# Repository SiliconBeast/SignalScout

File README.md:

# Signal Scout

A pocket RF field instrument: Wi-Fi/Bluetooth diagnostics, broadband RF presence sensing and a GPS + LoRa mesh safety beacon in one handheld. Hardware, enclosure and firmware live in this repository.

It runs **SignalOS**: a lock screen and always-on display, a pull-down shade, notifications, gestures with button equivalents, and two profiles (Hackerspace and Adventure). It joins Wi-Fi for time, weather and over-the-air updates. Design notes: [docs/SIGNALOS.md](docs/SIGNALOS.md).

| Hackerspace | Today | Shade | Always-on | Adventure | Weather |
|---|---|---|---|---|---|
|  |  |  |  |  |  |

**Try it in a browser:** `web/` is the real SignalOS UI compiled to WebAssembly inside a clickable device frame, with touch and gestures. Run `python3 -m http.server -d web 8000` and open http://localhost:8000. Rebuild it with `tools/build_web.sh` (needs `pip install ziglang`).

All 30 screens are in [docs/screenshots](docs/screenshots). The simulator renders them from the same UI code that runs on the device, driving it with scripted button presses and touch gestures.

## Hardware

**Base unit** (`SignalScout_Base/`, 46 x 82 mm, 4-layer)

| Function | Part |
|---|---|
| MCU | ESP32-S3-WROOM-1-N16R8 |
| Display | TOQ206XVT-01 2.06" AMOLED, QSPI |
| LoRa | Ebyte E22-900M22S (SX1262), 915 MHz |
| GNSS | u-blox MAX-M10S |
| Inputs | D-pad, A, B, side, SOS, lock slide switch (AW9523B expander) |
| Sensors | LSM6DSO IMU, BME280 |
| Feedback | DRV2605L + LRA, PAM8904 + piezo siren, RGB LED |
| Power | BQ24074 charger, MAX17048 fuel gauge, TPS63001 3.3 V |
| I/O | microSD, Qwiic, USB-C, pogo link to the sled |

**Sled** (`SignalScout_Sled.kicad_pcb`): carries the Arduino UNO Q and an AD8317 log detector (1 MHz to 10 GHz) on a U.FL antenna, plus its own battery, charger and 5 V boost. It links to the base through pogo pins: UART, I2C (sled ID EEPROM and fuel gauge) and a wake line.

**Enclosure**: `enclosure/` (STEP and STL).

### Pin map

Generated from the KiCad boards by `tools/gen_pins.py`, which also writes `firmware/include/pins.h`. The board files are the source of truth.

<!-- PINMAP:BEGIN -->
#### ESP32-S3-WROOM-1 (base board U1)

| Net | Module pad | GPIO | Note |
|---|---|---|---|
| `SD_CS` | 27 | IO0 | Strapping pin: boot mode |
| `LORA_RXEN` | 39 | IO1 |  |
| `GNSS_TXD` | 38 | IO2 |  |
| `SIREN_PWM` | 15 | IO3 | Strapping pin: JTAG select |
| `I2C_SDA` | 4 | IO4 |  |
| `I2C_SCL` | 5 | IO5 |  |
| `TP_INT` | 6 | IO6 |  |
| `DISP_TE` | 7 | IO7 |  |
| `DISP_RESET` | 12 | IO8 |  |
| `LCD_D3` | 17 | IO9 |  |
| `LCD_CS` | 18 | IO10 |  |
| `LCD_D0` | 19 | IO11 |  |
| `LCD_SCK` | 20 | IO12 |  |
| `LCD_D1` | 21 | IO13 |  |
| `LCD_D2` | 22 | IO14 |  |
| `EXP_INT` | 8 | IO15 |  |
| `SPI_MISO` | 9 | IO16 |  |
| `SPI_MOSI` | 10 | IO17 |  |
| `SPI_SCK` | 11 | IO18 |  |
| `USB_D-` | 13 | IO19 |  |
| `USB_D+` | 14 | IO20 |  |
| `KEY_SOS` | 23 | IO21 |  |
| `LORA_NSS` | 31 | IO38 |  |
| `LORA_BUSY` | 32 | IO39 |  |
| `LORA_DIO1` | 33 | IO40 |  |
| `LORA_NRST` | 34 | IO41 |  |
| `GNSS_RXD` | 35 | IO42 |  |
| `SLED_TX` | 37 | IO43 |  |
| `SLED_RX` | 36 | IO44 |  |
| `HAPTIC_EN` | 26 | IO45 | Strapping pin: VDD_SPI voltage |
| `SIREN_EN` | 16 | IO46 | Strapping pin: boot mode / ROM log |
| `SLED_SDA` | 24 | IO47 |  |
| `SLED_SCL` | 25 | IO48 |  |

#### AW9523B I/O expander (base board U4, I2C 0x58)

| Net | Port pin |
|---|---|
| `KEY_UP` | P0_0 |
| `KEY_DOWN` | P0_1 |
| `KEY_LEFT` | P0_2 |
| `KEY_RIGHT` | P0_3 |
| `KEY_A` | P0_4 |
| `KEY_B` | P0_5 |
| `SPARE_IO` | P0_6 |
| `KEY_SIDE` | P0_7 |
| `KEY_LOCK` | P1_0 |
| `CHG_N` | P1_1 |
| `SLED_WAKE` | P1_2 |
| `DISP_PWR_EN` | P1_3 |
| `GNSS_RST` | P1_4 |
| `LED_RK` | P1_5 |
| `LED_GK` | P1_6 |
| `LED_BK` | P1_7 |

#### UNO Q headers (sled A1)

| Net | UNO pin |
|---|---|
| `AD_VOUT` | A0 |
| `UNOQ_RX` | D0 |
| `UNOQ_TX` | D1 |
| `UNOQ_WAKE` | D2 |
<!-- PINMAP:END -->

## What it does

**Wi-Fi, Channels and Bluetooth** scan Wi-Fi and Bluetooth LE passively. Networks are listed by signal strength with channel, band and security. The Channels tab shows 2.4 GHz channel load and the least congested of channels 1/6/11. Press A on a network for its details and a signal-over-time graph.

**Sweep** shows the broadband RF level from the sled's detector as a number, a meter and a 30-second history. The level is compared with the Wi-Fi/BLE emitters the unit can see:

- *Quiet*: at the noise floor.
- *Explained*: consistent with the visible Wi-Fi/BLE activity.
- *Unexplained*: clearly more energy than the visible emitters account for.

It reports how much energy is present, not what the source is. The detector is broadband, so it cannot tell frequency or identify a transmitter.

**Position, Navigate and Mesh** show the GNSS fix, save waypoints, and point back to a saved waypoint with distance and bearing. It sends short text messages over a LoRa mesh (no subscription, peer to peer). Holding the SOS button for 2 seconds broadcasts the position to the mesh every 20 seconds and sounds the siren; hold again to cancel. SOS works from any screen and with the lock switch on.

**Weather** shows the online forecast (hourly and 3 days, Open-Meteo) when the unit is on Wi-Fi. It always shows a barometer forecast from the BME280 pressure trend, which works offline.

**Console** starts a hotspot with a join QR code. From any browser you can download logs and waypoints, add Wi-Fi networks, edit settings and upload firmware.

**Updates** checks GitHub releases. The download goes to the spare flash slot and is verified with SHA-256, and the bootloader rolls back automatically if the new version fails.

**Also**: Torch (white or red), Level, Settings, status bar with a live-activity pill, deep sleep, CSV logs on the card.

**Scope**: receive and analyse, plus the unit's own LoRa messages. The firmware has no deauthentication, jamming or spoofing features.

### Controls

| Control | Action |
|---|---|
| D-pad | Move focus; Left/Right switch tabs or change a setting |
| A | Select; hold on an app icon for quick actions; unlock |
| B | Back; hold for home |
| Side button | Home; on the launcher, opens the shade |
| SOS (hold 2 s) | Start or cancel SOS |
| Lock switch | Always-on display, keys ignored (SOS still works) |
| Touch | Tap; swipe down from the top for the shade, up from the bottom for home, right from the left edge for back; long-press an icon |

## What's next

Most new features can ship as over-the-air updates. First in line:

- **Safety:** Meshtastic compatibility, fall or crash detection with auto-SOS, a dead-man check-in timer, unknown BLE tracker detection.
- **Installers:** a Wi-Fi site-survey heat map, RF fingerprinting from detector burst timing, network health checks.
- **Outdoors:** breadcrumb track-back, GPX trips, offline maps, haptic navigation.
- **Platform:** a phone companion over BLE for free-text messages, and installable script apps.

Hardware additions (magnetometer, SDR, NFC, satellite) would come as sleds. Full list: [docs/ROADMAP.md](docs/ROADMAP.md).

## Repository layout

| Path | Contents |
|---|---|
| `firmware/` | ESP32-S3 firmware, simulator and unit tests (PlatformIO) |
| `firmware/lib/ss_core` | Portable logic: pogo protocol, mesh, correlation, battery, geo, UBX, weather, OTA manifest, JSON, calendar |
| `firmware/lib/ss_services` | Services, one per subsystem, running on the HAL |
| `firmware/lib/ss_ui` | SignalOS (LVGL 9): shell, apps, theme, generated fonts and icons |
| `firmware/lib/ss_mock` | Mock for every HAL interface (simulator and tests) |
| `firmware/src/device` | ESP32-S3 drivers and FreeRTOS tasks |
| `firmware/src/sim` | Desktop simulator and screenshot renderer |
| `firmware/src/web`, `web/` | Browser simulator (WebAssembly) in a device frame |
| `sled/signalscout_sled` | Arduino App Lab app for the UNO Q (sketch + Python) |
| `assets/` | Icon tiles (PNG, both profiles) and fonts (OFL) |
| `docs/` | [SignalOS](docs/SIGNALOS.md), [roadmap](docs/ROADMAP.md), [bring-up checklist](docs/BRINGUP.md), [protocol](docs/PROTOCOL.md), [hardware-verification list](docs/TODO.md), [pin map](docs/PINMAP.md) |
| `tools/` | Pin-map, icon, font and test-vector generators, shared-file sync, release manifest |

## Firmware design

- **PlatformIO + Arduino-ESP32.** The Arduino core gives working Wi-Fi scan, NimBLE, SD and RadioLib support with little glue. The one place where it would cost performance, the QSPI display, uses the ESP-IDF SPI driver directly (`src/device/display.cpp`), which the Arduino core exposes.
- **HAL.** `lib/ss_core/hal.h` has one interface per peripheral. Device implementations are in `src/device`, mocks in `lib/ss_mock`.
- **Services.** One per subsystem (input, housekeeping, scan, sweep, GNSS, mesh, storage, network). On the device each runs in its own FreeRTOS task.
- **Display.** Two 40-row DMA buffers so LVGL renders while the previous strip is on the wire; brightness changes are applied between flushes.
- **Message bus.** The UI pops `Event`s and pushes `Cmd`s and never touches a driver or a service.
- **LoRa mesh.** RadioLib SX1262 at 500 kHz bandwidth, SF9. Managed flooding with a hop limit, duplicate suppression, random relay delay, SOS priority and a self-imposed 10 % airtime budget (SOS may exceed it).
- **GNSS.** UBX only: CFG-VALSET at boot (NAV-PVT at 1 Hz, GPS + Galileo + BeiDou, optional power save).
- **Sled.** The STM32 samples the detector and streams it to the base. The Linux side scans Wi-Fi/BLE and sends a verdict. If the Linux side is not running, the base runs the same comparison on its own scan.

## Build and flash

Install [PlatformIO Core](https://docs.platformio.org/en/latest/core/installation/index.html), then from `firmware/`:

```sh
pio run -e device                 # build
pio run -e device -t upload       # flash over USB-C
pio device monitor                # serial log (USB CDC)
pio test -e native                # unit tests on the host
pio run -e sim                    # simulator (needs libsdl2-dev)
.pio/build/sim/program            # interactive: arrows, Z = A, X = B, H = side, S = SOS, L = lock, mouse = touch
.pio/build/sim/program --shots ../docs/screenshots
```

If the board does not enter the bootloader by itself, hold BOOT, tap EN, release BOOT.

A plain CMake build of the tests and simulator is also available (`firmware/CMakeLists.txt`).

**Sled**: open `sled/signalscout_sled` in Arduino App Lab and run it on the UNO Q. Run `python3 tools/sync_shared.py` first if you changed `proto.h`.

After a hardware change run `python3 tools/gen_pins.py`. Do not edit `pins.h` by hand. Icons: `python3 tools/gen_icons.py`; fonts: `tools/gen_fonts.sh` (needs `npm i -g lv_font_conv`).

**Releases**: bump `SS_FW_VERSION` in `firmware/include/board.h`, then tag `v<version>`. The release workflow publishes `firmware.bin` and `manifest.json`, and devices offer the update.

## Status and known limitations

The logic, UI and protocol are tested on the host (39 firmware tests, 7 sled tests) and the device firmware builds in CI. **Nothing here has run on the real boards yet.** Follow [docs/BRINGUP.md](docs/BRINGUP.md) for first power-on; [docs/TODO.md](docs/TODO.md) lists what needs hardware to confirm.

- The display driver assumes the panel uses a CO5300 controller at 410 x 502 with a 22-column offset. Confirm against the panel datasheet.
- The Sweep detector is broadband and uncalibrated until the constants in the sled sketch are set against a known source.
- The navigation arrow uses GPS course over ground, so it only settles while moving. There is no magnetometer.
- Messages are canned quick replies; there is no keyboard.
- Touch assumes an FT3168 or CST816 class controller (both probed) with axes matching the panel. Confirm during bring-up.
- Over-the-air updates need a published release; until then the Updates app reports that it couldn't check.
- LoRa settings target the 902 to 928 MHz band (Canada/US). Check local rules before using it elsewhere.

## Contributing

See [CONTRIBUTING.md](CONTRIBUTING.md). Report security problems as described in [SECURITY.md](SECURITY.md).

## License

MIT, Copyright (c) 2026 Suvir Duggal. See [LICENSE](LICENSE). Covers the firmware, tools, PCB and enclosure files, and docs. The bundled Space Grotesk and JetBrains Mono fonts keep their own SIL Open Font License (see `assets/fonts/`).

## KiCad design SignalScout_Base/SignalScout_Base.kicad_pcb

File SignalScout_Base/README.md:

# Base board

KiCad project for the base unit (46 x 82 mm, 4-layer): ESP32-S3, AMOLED display, LoRa, GNSS, sensors, inputs and power.

Schematic sheets: `mcu`, `display`, `radio`, `sensors`, `controls`, `power`. Pin assignments are exported to the firmware by `tools/gen_pins.py`.

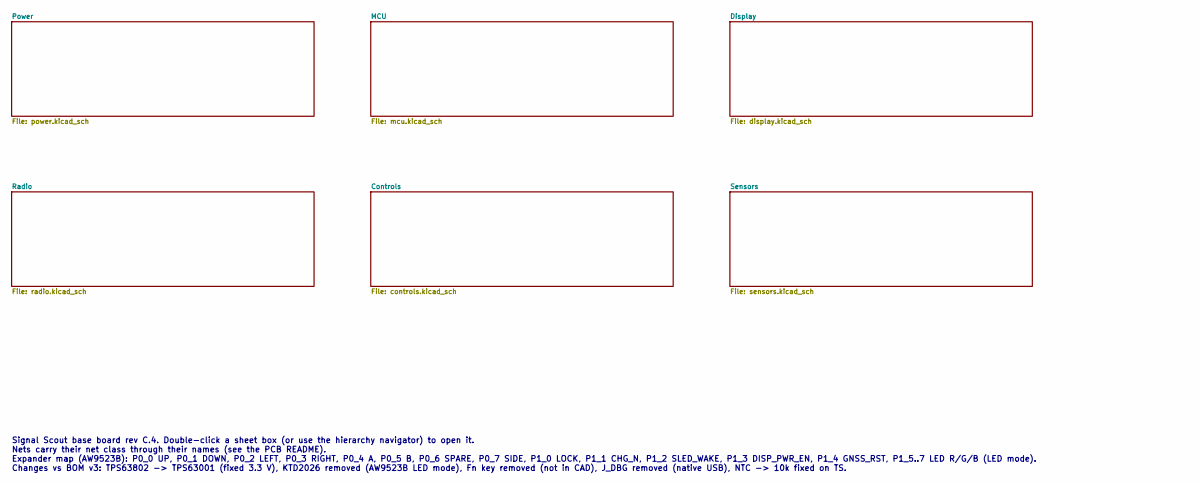
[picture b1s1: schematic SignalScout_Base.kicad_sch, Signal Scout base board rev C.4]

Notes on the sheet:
Signal Scout base board rev C.4. Double-click a sheet box (or use the hierarchy navigator) to open it. Nets carry their net class through their names (see the PCB README). Expander map (AW9523B): P0_0 UP, P0_1 DOWN, P0_2 LEFT, P0_3 RIGHT, P0_4 A, P0_5 B, P0_6 SPARE, P0_7 SIDE, P1_0 LOCK, P1_1 CHG_N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

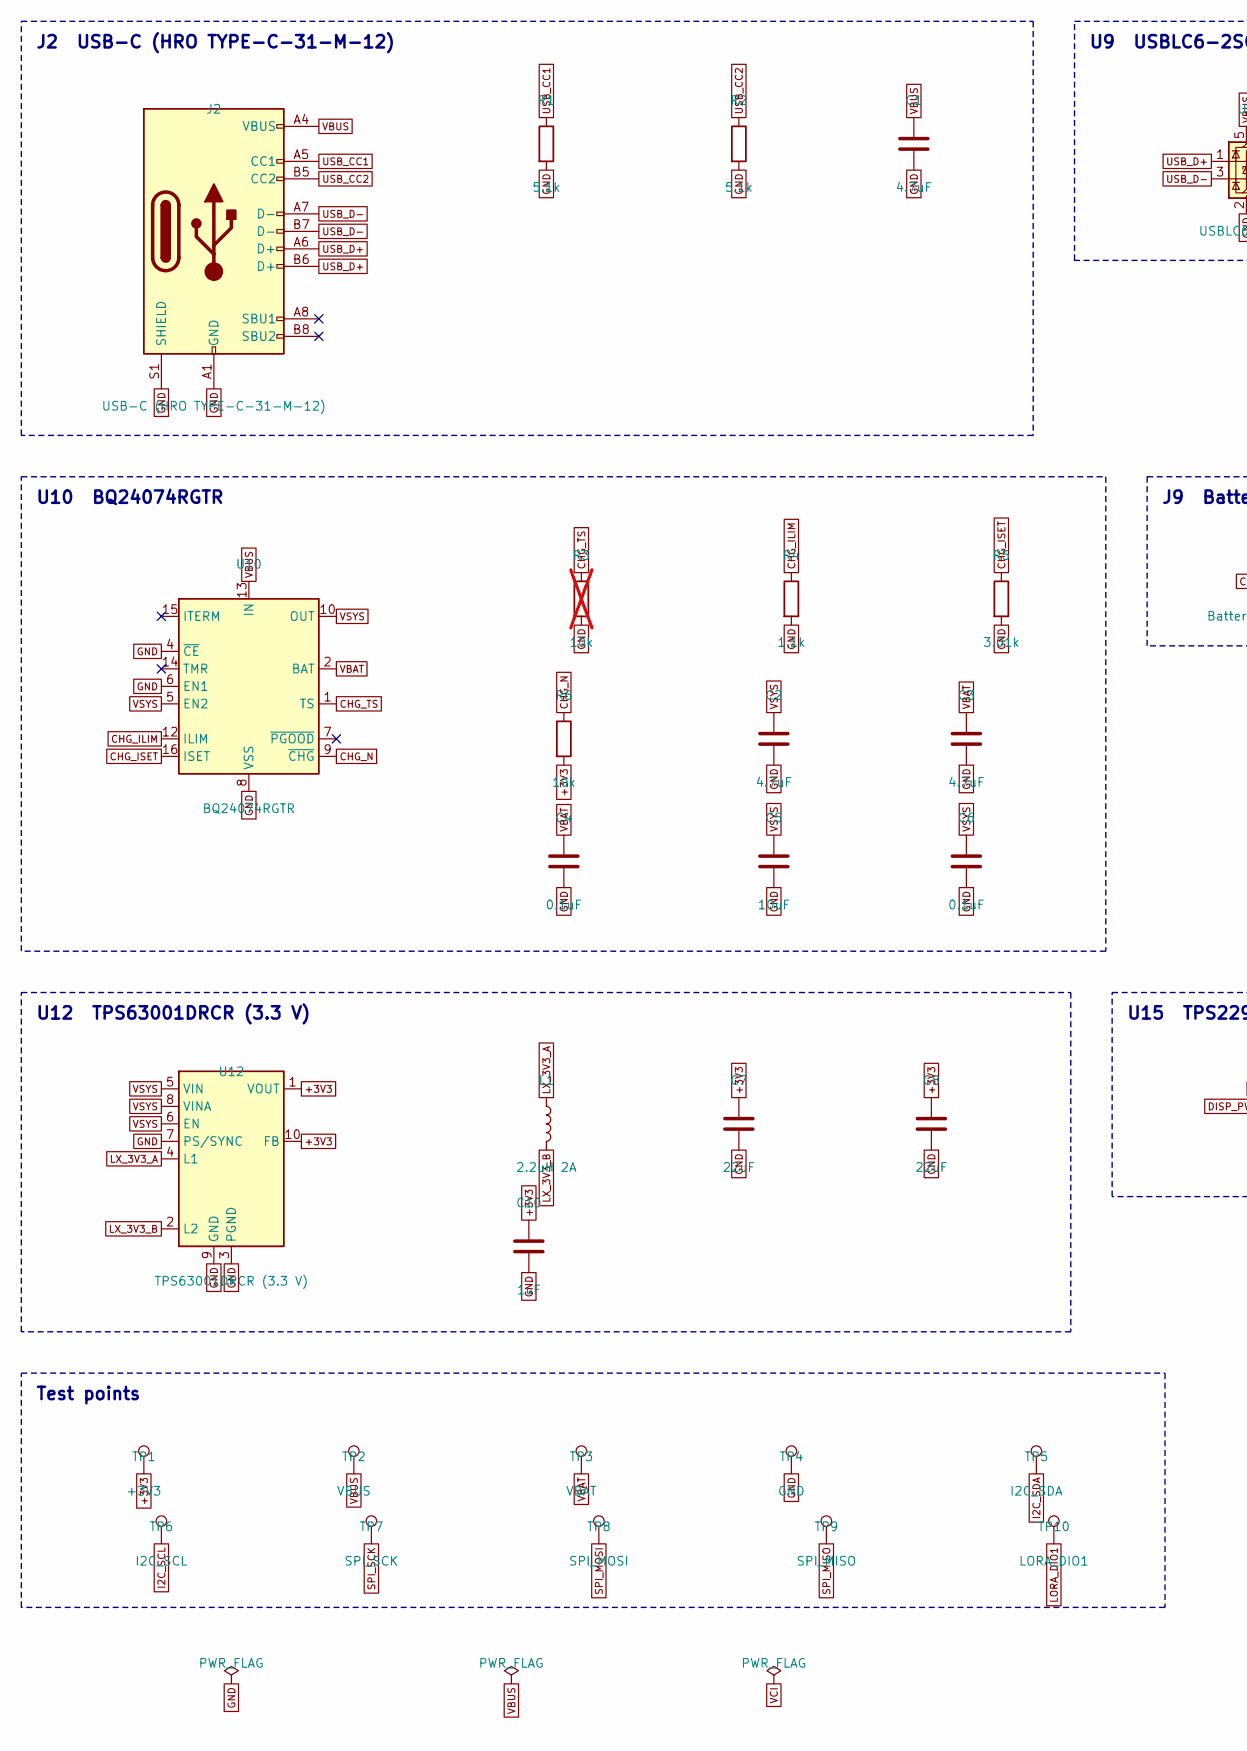
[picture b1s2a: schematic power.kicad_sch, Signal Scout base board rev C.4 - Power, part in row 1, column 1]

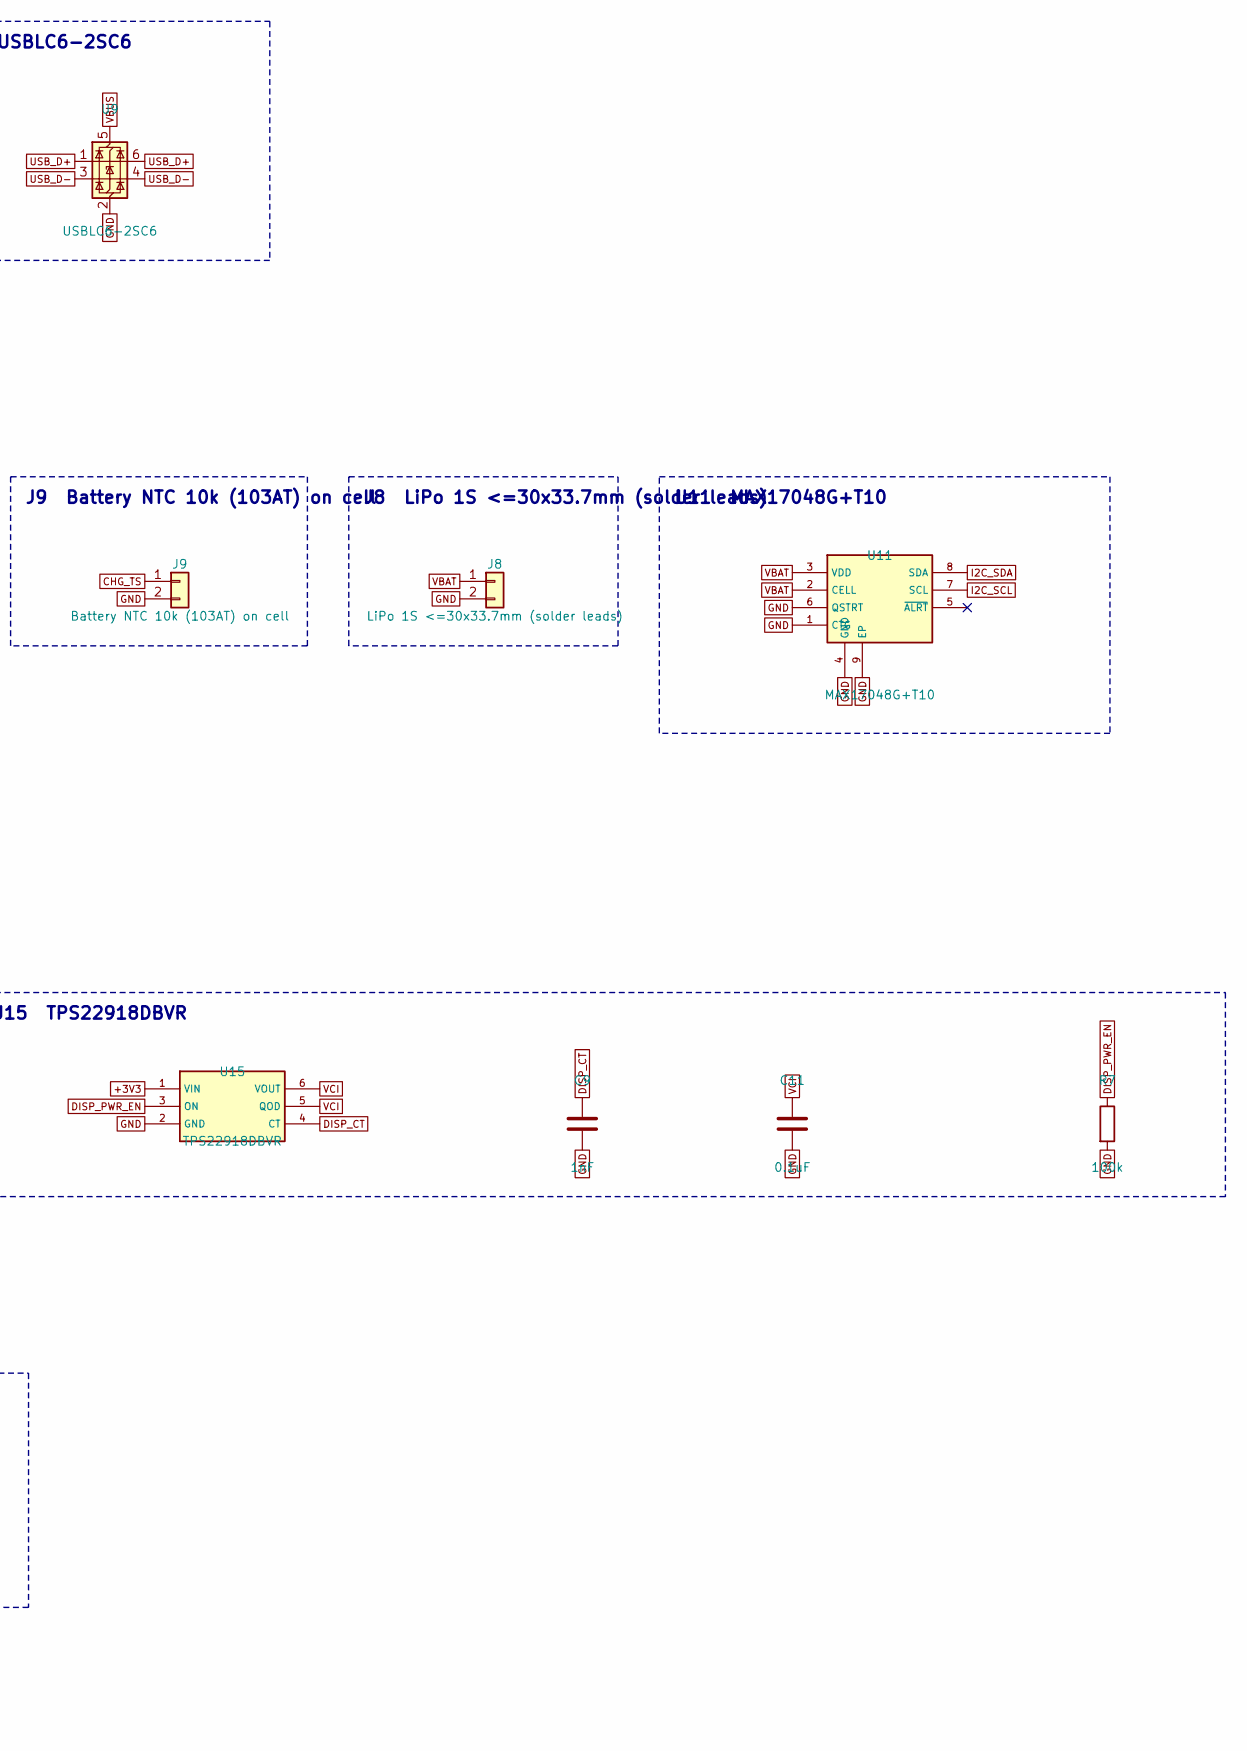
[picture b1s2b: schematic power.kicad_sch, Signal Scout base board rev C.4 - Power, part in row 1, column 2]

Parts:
C1, C2, C3: 4.7uF; C_0603_1608Metric
C4, C6, C11: 0.1uF; C_0402_1005Metric
C5: 10uF; C_0805_2012Metric
C7, C8: 22uF; C_0805_2012Metric
C9: 1nF; C_0402_1005Metric
C10: 1uF; C_0402_1005Metric
J2: USB-C (HRO TYPE-C-31-M-12); USB_C_Receptacle_HRO_TYPE-C-31-M-12
J8: LiPo 1S <=30x33.7mm (solder leads); SolderWire-0.25sqmm_1x02_P4.2mm_D0.65mm_OD1.7mm
J9: Battery NTC 10k (103AT) on cell; JST_SH_SM02B-SRSS-TB_1x02-1MP_P1.00mm_Horizontal
L1: 2.2uH 2A; L_1210_3225Metric
R1, R2: 5.1k; R_0402_1005Metric
R3: 10k; R_0402_1005Metric; not fitted
R4: 1.1k; R_0402_1005Metric
R5: 3.01k; R_0402_1005Metric
R6: 10k; R_0402_1005Metric
R7: 100k; R_0402_1005Metric
TP1: +3V3; TestPoint_Pad_D1.0mm
TP2: VBUS; TestPoint_Pad_D1.0mm
TP3: VBAT; TestPoint_Pad_D1.0mm
TP4: GND; TestPoint_Pad_D1.0mm
TP5: I2C_SDA; TestPoint_Pad_D1.0mm
TP6: I2C_SCL; TestPoint_Pad_D1.0mm
TP7: SPI_SCK; TestPoint_Pad_D1.0mm
TP8: SPI_MOSI; TestPoint_Pad_D1.0mm
TP9: SPI_MISO; TestPoint_Pad_D1.0mm
TP10: LORA_DIO1; TestPoint_Pad_D1.0mm
U9: USBLC6-2SC6; SOT-23-6
U10: BQ24074RGTR; VQFN-16-1EP_3x3mm_P0.5mm_EP1.6x1.6mm
U11: MAX17048G+T10; TDFN-8-1EP_2x2mm_P0.5mm_EP0.8x1.2mm
U12: TPS63001DRCR (3.3 V); Texas_DRC0010J
U15: TPS22918DBVR; SOT-23-6

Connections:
+3V3: C7.1, C8.1, C10.1, R6.2, TP1.1, U12.1 (VOUT), U12.10 (FB), U15.1 (VIN); also elsewhere on the board
CHG_ILIM: R4.1, U10.12 (ILIM)
CHG_ISET: R5.1, U10.16 (ISET)
CHG_N: R6.1, U10.9 (~CHG); also elsewhere on the board
CHG_TS: J9.1, R3.1, U10.1 (TS)
DISP_CT: C9.1, U15.4 (CT)
DISP_PWR_EN: R7.1, U15.3 (ON); also elsewhere on the board
GND: C1.2, C2.2, C3.2, C4.2, C5.2, C6.2, C7.2, C8.2, C9.2, C10.2, C11.2, J2.A1 (GND), J2.A12 (GND), J2.B1 (GND), J2.B12 (GND), J2.S1 (SHIELD), J8.2, J9.2, R1.2, R2.2, R3.2, R4.2, R5.2, R7.2, TP4.1, U9.2 (GND), U10.4 (~CE), U10.6 (EN1), U10.8 (VSS), U10.17 (VSS), U11.1 (CTG), U11.4 (GND), U11.6 (QSTRT), U11.9 (EP), U12.3 (PGND), U12.7 (PS/SYNC), U12.9 (GND), U12.11 (PGND), U15.2 (GND); also elsewhere on the board
I2C_SCL: TP6.1, U11.7 (SCL); also elsewhere on the board
I2C_SDA: TP5.1, U11.8 (SDA); also elsewhere on the board
LORA_DIO1: TP10.1; also elsewhere on the board
LX_3V3_A: L1.1, U12.4 (L1)
LX_3V3_B: L1.2, U12.2 (L2)
SPARE_IO: U10.7 (~PGOOD); also elsewhere on the board
SPI_MISO: TP9.1; also elsewhere on the board
SPI_MOSI: TP8.1; also elsewhere on the board
SPI_SCK: TP7.1; also elsewhere on the board
USB_CC1: J2.A5 (CC1), R1.1
USB_CC2: J2.B5 (CC2), R2.1
USB_D+: J2.A6 (D+), J2.B6 (D+), U9.1 (I/O1), U9.6 (I/O1); also elsewhere on the board
USB_D-: J2.A7 (D-), J2.B7 (D-), U9.3 (I/O2), U9.4 (I/O2); also elsewhere on the board
VBAT: C3.1, C4.1, J8.1, TP3.1, U10.2 (BAT), U10.3 (BAT), U11.2 (CELL), U11.3 (VDD); also elsewhere on the board
VBUS: C1.1, J2.A4 (VBUS), J2.A9 (VBUS), J2.B4 (VBUS), J2.B9 (VBUS), TP2.1, U9.5 (VBUS), U10.13 (IN); also elsewhere on the board
VCI: C11.1, U15.5 (QOD), U15.6 (VOUT); also elsewhere on the board
VSYS: C2.1, C5.1, C6.1, U10.5 (EN2), U10.10 (OUT), U10.11 (OUT), U12.5 (VIN), U12.6 (EN), U12.8 (VINA); also elsewhere on the board

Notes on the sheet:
J2 USB-C (HRO TYPE-C-31-M-12)
U9 USBLC6-2SC6
U10 BQ24074RGTR
J9 Battery NTC 10k (103AT) on cell
J8 LiPo 1S <=30x33.7mm (solder leads)
U11 MAX17048G+T10
U12 TPS63001DRCR (3.3 V)
U15 TPS22918DBVR
Test points

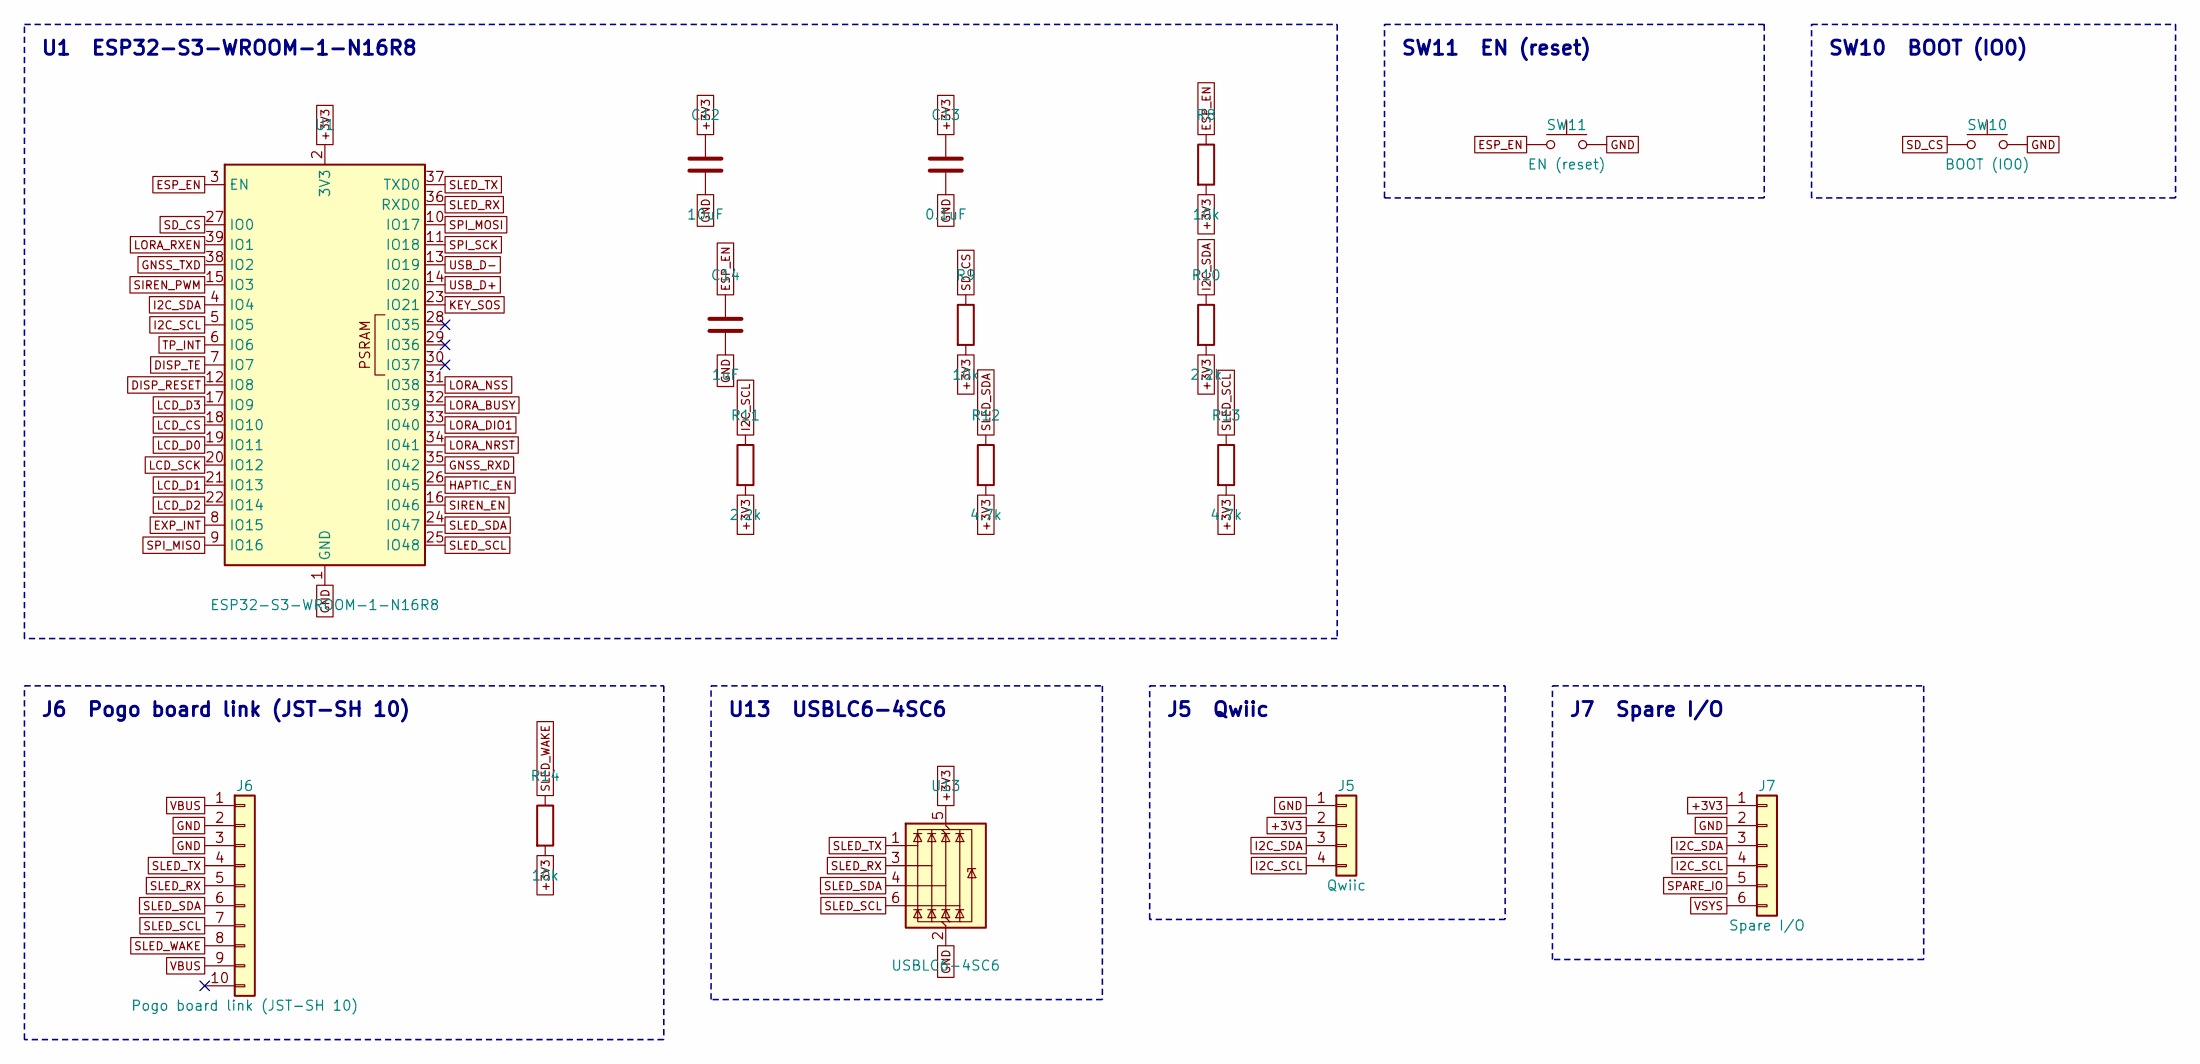
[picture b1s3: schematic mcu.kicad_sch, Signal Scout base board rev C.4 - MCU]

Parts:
C12: 10uF; C_0805_2012Metric
C13: 0.1uF; C_0402_1005Metric
C14: 1uF; C_0402_1005Metric
J5: Qwiic; JST_SH_SM04B-SRSS-TB_1x04-1MP_P1.00mm_Horizontal
J6: Pogo board link (JST-SH 10); JST_SH_SM10B-SRSS-TB_1x10-1MP_P1.00mm_Horizontal
J7: Spare I/O; PinHeader_1x06_P1.27mm_Vertical
R8, R9, R14: 10k; R_0402_1005Metric
R10, R11: 2.2k; R_0402_1005Metric
R12, R13: 4.7k; R_0402_1005Metric
SW10: BOOT (IO0); SW_SPST_B3U-1000P
SW11: EN (reset); SW_SPST_B3U-1000P
U1: ESP32-S3-WROOM-1-N16R8; ESP32-S3-WROOM-1
U13: USBLC6-4SC6; SOT-23-6

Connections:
+3V3: C12.1, C13.1, J5.2, J7.1, R8.2, R9.2, R10.2, R11.2, R12.2, R13.2, R14.2, U1.2 (3V3), U13.5 (VBUS); also elsewhere on the board
DISP_RESET: U1.12 (IO8); also elsewhere on the board
DISP_TE: U1.7 (IO7); also elsewhere on the board
ESP_EN: C14.1, R8.1, SW11.1, U1.3 (EN)
EXP_INT: U1.8 (IO15); also elsewhere on the board
GND: C12.2, C13.2, C14.2, J5.1, J6.2, J6.3, J7.2, SW10.2, SW11.2, U1.1 (GND), U1.40 (GND), U1.41 (GND), U13.2 (GND); also elsewhere on the board
GNSS_RXD: U1.35 (IO42); also elsewhere on the board
GNSS_TXD: U1.38 (IO2); also elsewhere on the board
HAPTIC_EN: U1.26 (IO45); also elsewhere on the board
I2C_SCL: J5.4, J7.4, R11.1, U1.5 (IO5); also elsewhere on the board
I2C_SDA: J5.3, J7.3, R10.1, U1.4 (IO4); also elsewhere on the board
KEY_SOS: U1.23 (IO21); also elsewhere on the board
LCD_CS: U1.18 (IO10); also elsewhere on the board
LCD_D0: U1.19 (IO11); also elsewhere on the board
LCD_D1: U1.21 (IO13); also elsewhere on the board
LCD_D2: U1.22 (IO14); also elsewhere on the board
LCD_D3: U1.17 (IO9); also elsewhere on the board
LCD_SCK: U1.20 (IO12); also elsewhere on the board
LORA_BUSY: U1.32 (IO39); also elsewhere on the board
LORA_DIO1: U1.33 (IO40); also elsewhere on the board
LORA_NRST: U1.34 (IO41); also elsewhere on the board
LORA_NSS: U1.31 (IO38); also elsewhere on the board
LORA_RXEN: U1.39 (IO1); also elsewhere on the board
SD_CS: R9.1, SW10.1, U1.27 (IO0); also elsewhere on the board
SIREN_EN: U1.16 (IO46); also elsewhere on the board
SIREN_PWM: U1.15 (IO3); also elsewhere on the board
SLED_RX: J6.5, U1.36 (RXD0), U13.3 (I/O2)
SLED_SCL: J6.7, R13.1, U1.25 (IO48), U13.6 (I/O4)
SLED_SDA: J6.6, R12.1, U1.24 (IO47), U13.4 (I/O3)
SLED_TX: J6.4, U1.37 (TXD0), U13.1 (I/O1)
SLED_WAKE: J6.8, R14.1; also elsewhere on the board
SPARE_IO: J7.5; also elsewhere on the board
SPI_MISO: U1.9 (IO16); also elsewhere on the board
SPI_MOSI: U1.10 (IO17); also elsewhere on the board
SPI_SCK: U1.11 (IO18); also elsewhere on the board
TP_INT: U1.6 (IO6); also elsewhere on the board
USB_D+: U1.14 (IO20); also elsewhere on the board
USB_D-: U1.13 (IO19); also elsewhere on the board
VBUS: J6.1, J6.9; also elsewhere on the board
VSYS: J7.6; also elsewhere on the board

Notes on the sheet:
U1 ESP32-S3-WROOM-1-N16R8
SW11 EN (reset)
SW10 BOOT (IO0)
J6 Pogo board link (JST-SH 10)
U13 USBLC6-4SC6
J5 Qwiic
J7 Spare I/O

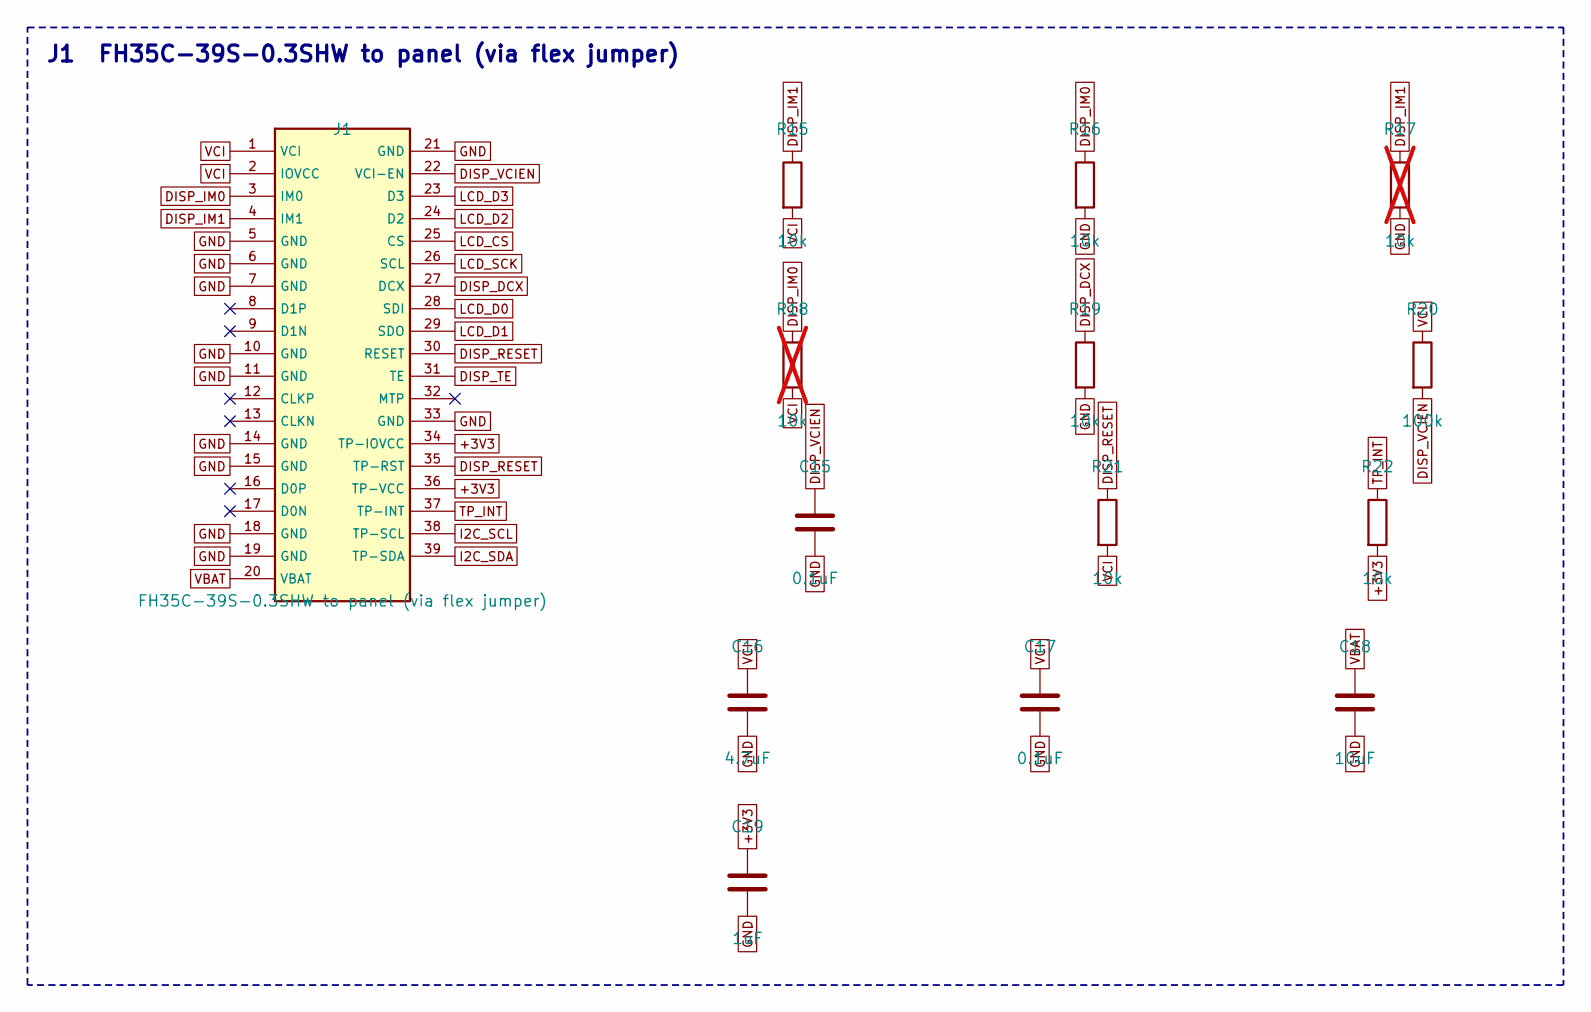
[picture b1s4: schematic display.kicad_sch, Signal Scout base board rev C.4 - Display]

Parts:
C15, C17: 0.1uF; C_0402_1005Metric
C16: 4.7uF; C_0603_1608Metric
C18: 10uF; C_0805_2012Metric
C19: 1uF; C_0402_1005Metric
J1: FH35C-39S-0.3SHW to panel (via flex jumper); Hirose_FH35C-39S-0.3SHW
R15, R16, R19, R21, R22: 10k; R_0402_1005Metric
R17, R18: 10k; R_0402_1005Metric; not fitted
R20: 100k; R_0402_1005Metric

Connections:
+3V3: C19.1, J1.34 (TP-IOVCC), J1.36 (TP-VCC), R22.2; also elsewhere on the board
DISP_DCX: J1.27 (DCX), R19.1
DISP_IM0: J1.3 (IM0), R16.1, R18.1
DISP_IM1: J1.4 (IM1), R15.1, R17.1
DISP_RESET: J1.30 (RESET), J1.35 (TP-RST), R21.1; also elsewhere on the board
DISP_TE: J1.31 (TE); also elsewhere on the board
DISP_VCIEN: C15.1, J1.22 (VCI-EN), R20.2
GND: C15.2, C16.2, C17.2, C18.2, C19.2, J1.5 (GND), J1.6 (GND), J1.7 (GND), J1.10 (GND), J1.11 (GND), J1.14 (GND), J1.15 (GND), J1.18 (GND), J1.19 (GND), J1.21 (GND), J1.33 (GND), R16.2, R17.2, R19.2; also elsewhere on the board
I2C_SCL: J1.38 (TP-SCL); also elsewhere on the board
I2C_SDA: J1.39 (TP-SDA); also elsewhere on the board
LCD_CS: J1.25 (CS); also elsewhere on the board
LCD_D0: J1.28 (SDI); also elsewhere on the board
LCD_D1: J1.29 (SDO); also elsewhere on the board
LCD_D2: J1.24 (D2); also elsewhere on the board
LCD_D3: J1.23 (D3); also elsewhere on the board
LCD_SCK: J1.26 (SCL); also elsewhere on the board
TP_INT: J1.37 (TP-INT), R22.1; also elsewhere on the board
VBAT: C18.1, J1.20 (VBAT); also elsewhere on the board
VCI: C16.1, C17.1, J1.1 (VCI), J1.2 (IOVCC), R15.2, R18.2, R20.1, R21.2; also elsewhere on the board

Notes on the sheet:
J1 FH35C-39S-0.3SHW to panel (via flex jumper)

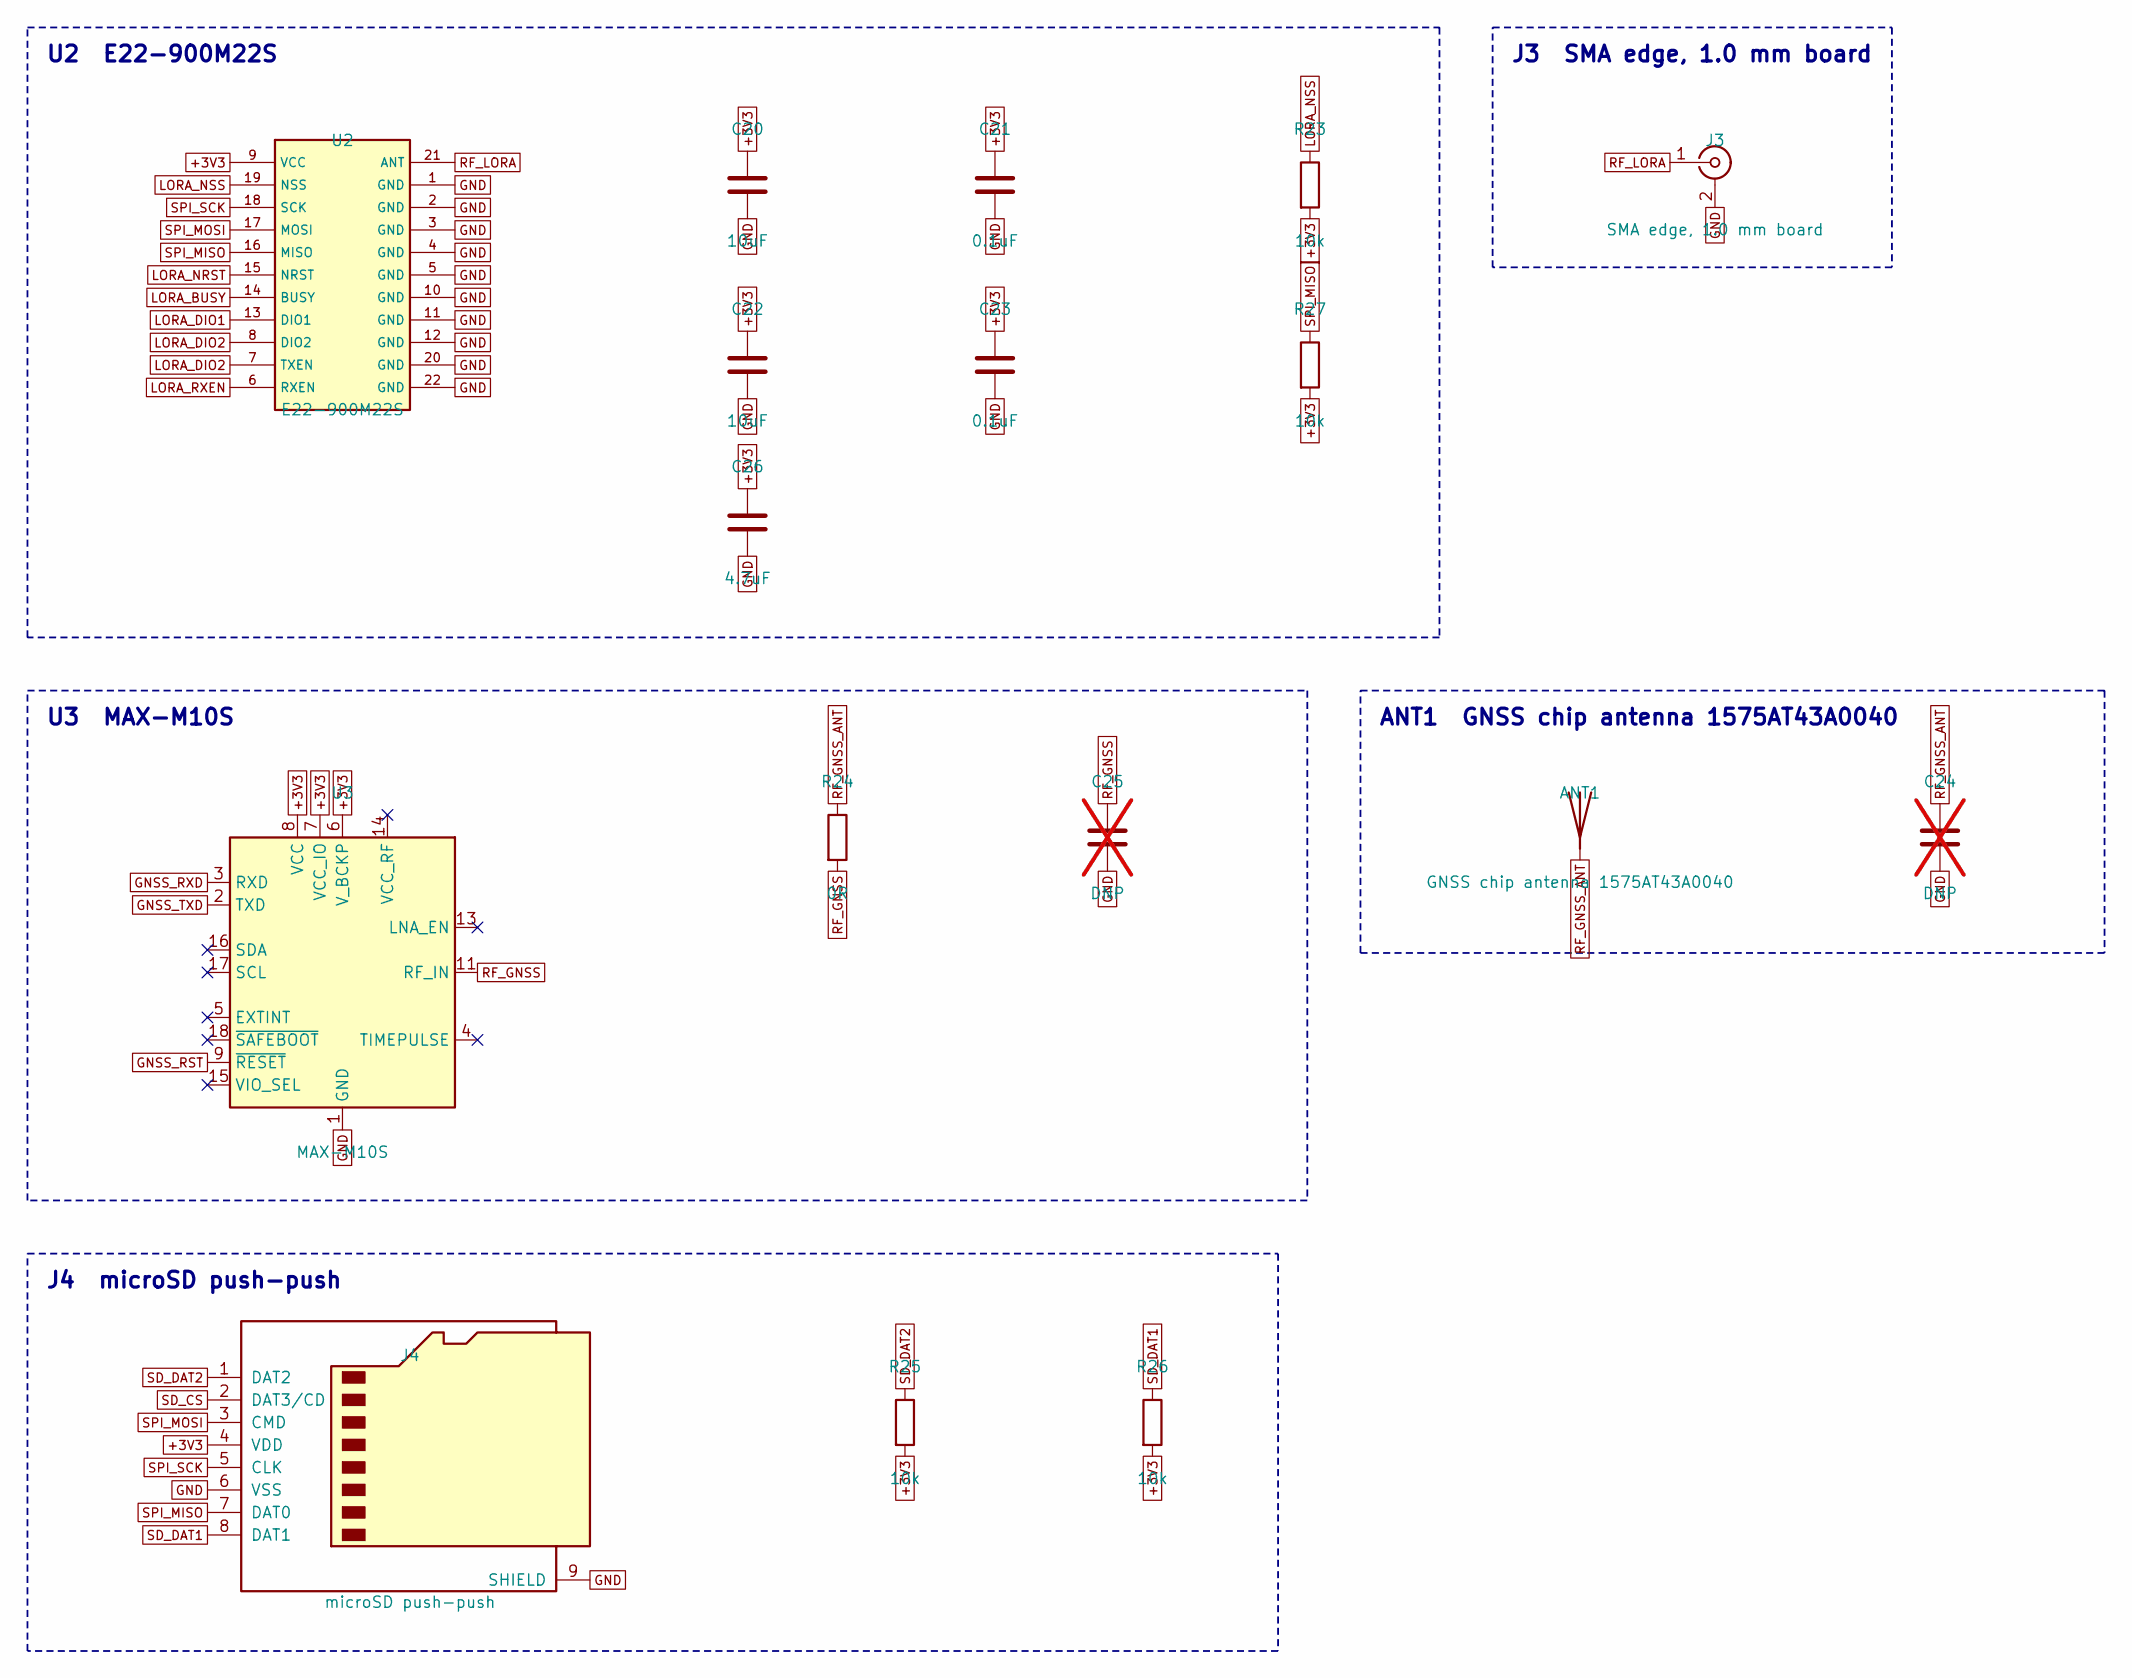
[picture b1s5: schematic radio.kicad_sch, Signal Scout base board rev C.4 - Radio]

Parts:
ANT1: GNSS chip antenna 1575AT43A0040; Johanson_1575AT43A0040
C20, C22: 10uF; C_0805_2012Metric
C21, C23: 0.1uF; C_0402_1005Metric
C24, C25: DNP; C_0402_1005Metric; not fitted
C26: 4.7uF; C_0603_1608Metric
J3: SMA edge, 1.0 mm board; SMA_Samtec_SMA-J-P-X-ST-EM1_EdgeMount
J4: microSD push-push; microSD_HC_Wuerth_693072010801
R23, R25, R26, R27: 10k; R_0402_1005Metric
R24: 0R; R_0402_1005Metric
U2: E22-900M22S
U3: MAX-M10S; ublox_MAX

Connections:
+3V3: C20.1, C21.1, C22.1, C23.1, C26.1, J4.4 (VDD), R23.2, R25.2, R26.2, R27.2, U2.9 (VCC), U3.6 (V_BCKP), U3.7 (VCC_IO), U3.8 (VCC); also elsewhere on the board
GND: C20.2, C21.2, C22.2, C23.2, C24.2, C25.2, C26.2, J3.2 (Ext), J4.6 (VSS), J4.9 (SHIELD), U2.1 (GND), U2.2 (GND), U2.3 (GND), U2.4 (GND), U2.5 (GND), U2.10 (GND), U2.11 (GND), U2.12 (GND), U2.20 (GND), U2.22 (GND), U3.1 (GND), U3.10 (GND), U3.12 (GND); also elsewhere on the board
GNSS_RST: U3.9 (~RESET); also elsewhere on the board
GNSS_RXD: U3.3 (RXD); also elsewhere on the board
GNSS_TXD: U3.2 (TXD); also elsewhere on the board
LORA_BUSY: U2.14 (BUSY); also elsewhere on the board
LORA_DIO1: U2.13 (DIO1); also elsewhere on the board
LORA_DIO2: U2.7 (TXEN), U2.8 (DIO2)
LORA_NRST: U2.15 (NRST); also elsewhere on the board
LORA_NSS: R23.1, U2.19 (NSS); also elsewhere on the board
LORA_RXEN: U2.6 (RXEN); also elsewhere on the board
RF_GNSS: C25.1, R24.2, U3.11 (RF_IN)
RF_GNSS_ANT: ANT1.1, C24.1, R24.1
RF_LORA: J3.1 (In), U2.21 (ANT)
SD_CS: J4.2 (DAT3/CD); also elsewhere on the board
SD_DAT1: J4.8 (DAT1), R26.1
SD_DAT2: J4.1 (DAT2), R25.1
SPI_MISO: J4.7 (DAT0), R27.1, U2.16 (MISO); also elsewhere on the board
SPI_MOSI: J4.3 (CMD), U2.17 (MOSI); also elsewhere on the board
SPI_SCK: J4.5 (CLK), U2.18 (SCK); also elsewhere on the board

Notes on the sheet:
U2 E22-900M22S
J3 SMA edge, 1.0 mm board
U3 MAX-M10S
ANT1 GNSS chip antenna 1575AT43A0040
J4 microSD push-push
